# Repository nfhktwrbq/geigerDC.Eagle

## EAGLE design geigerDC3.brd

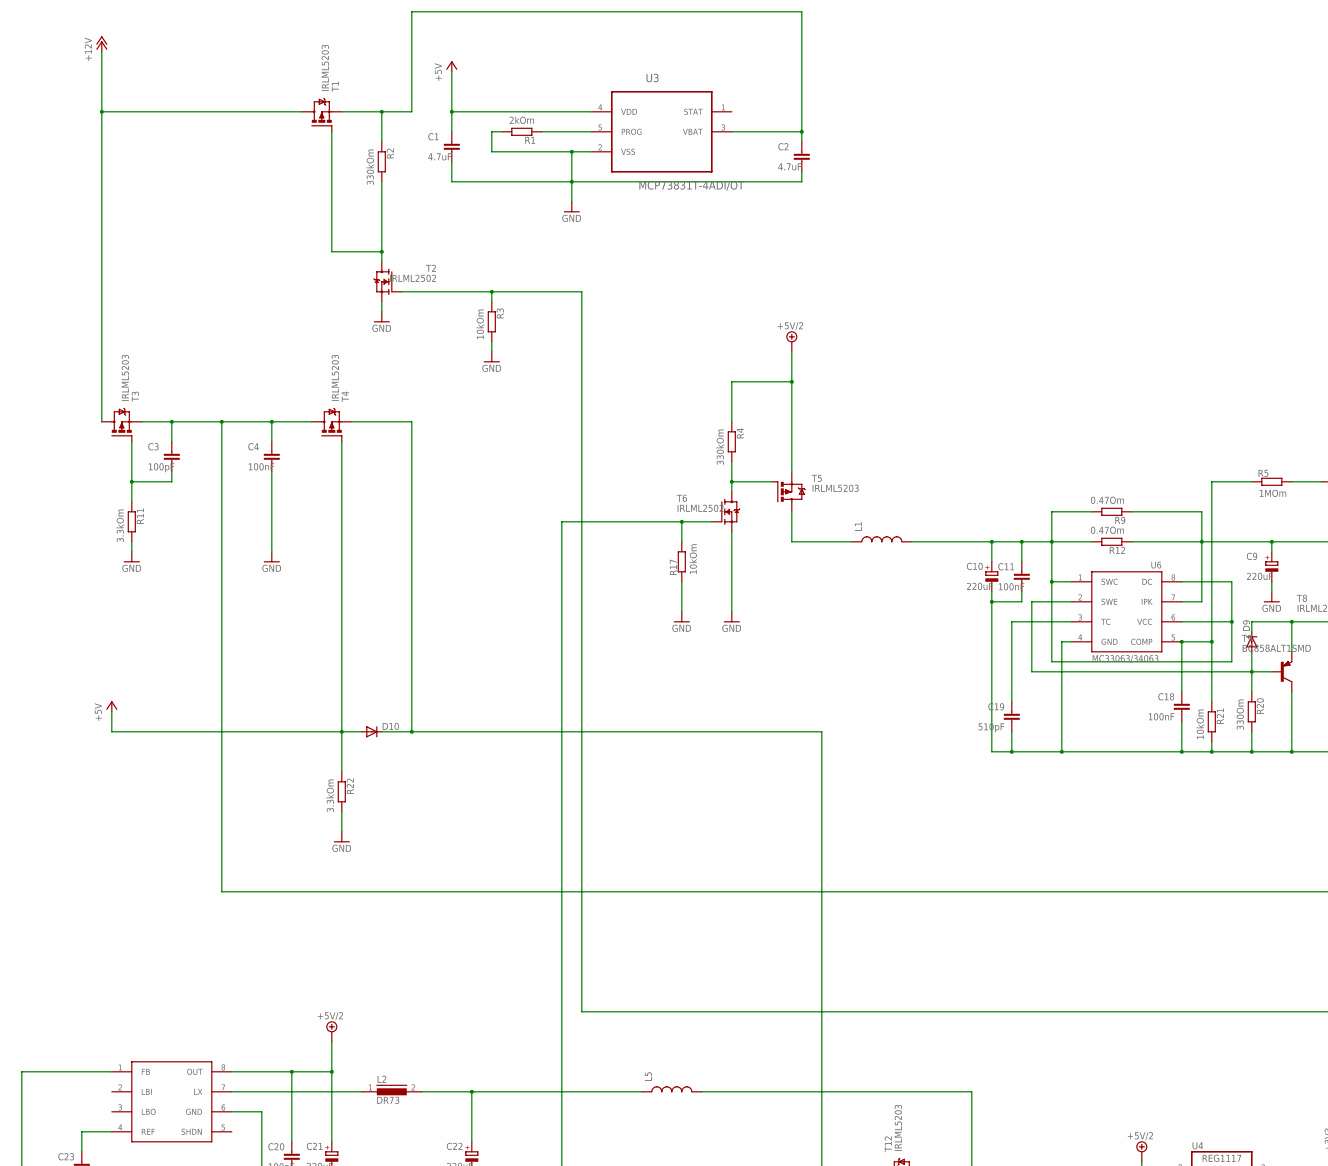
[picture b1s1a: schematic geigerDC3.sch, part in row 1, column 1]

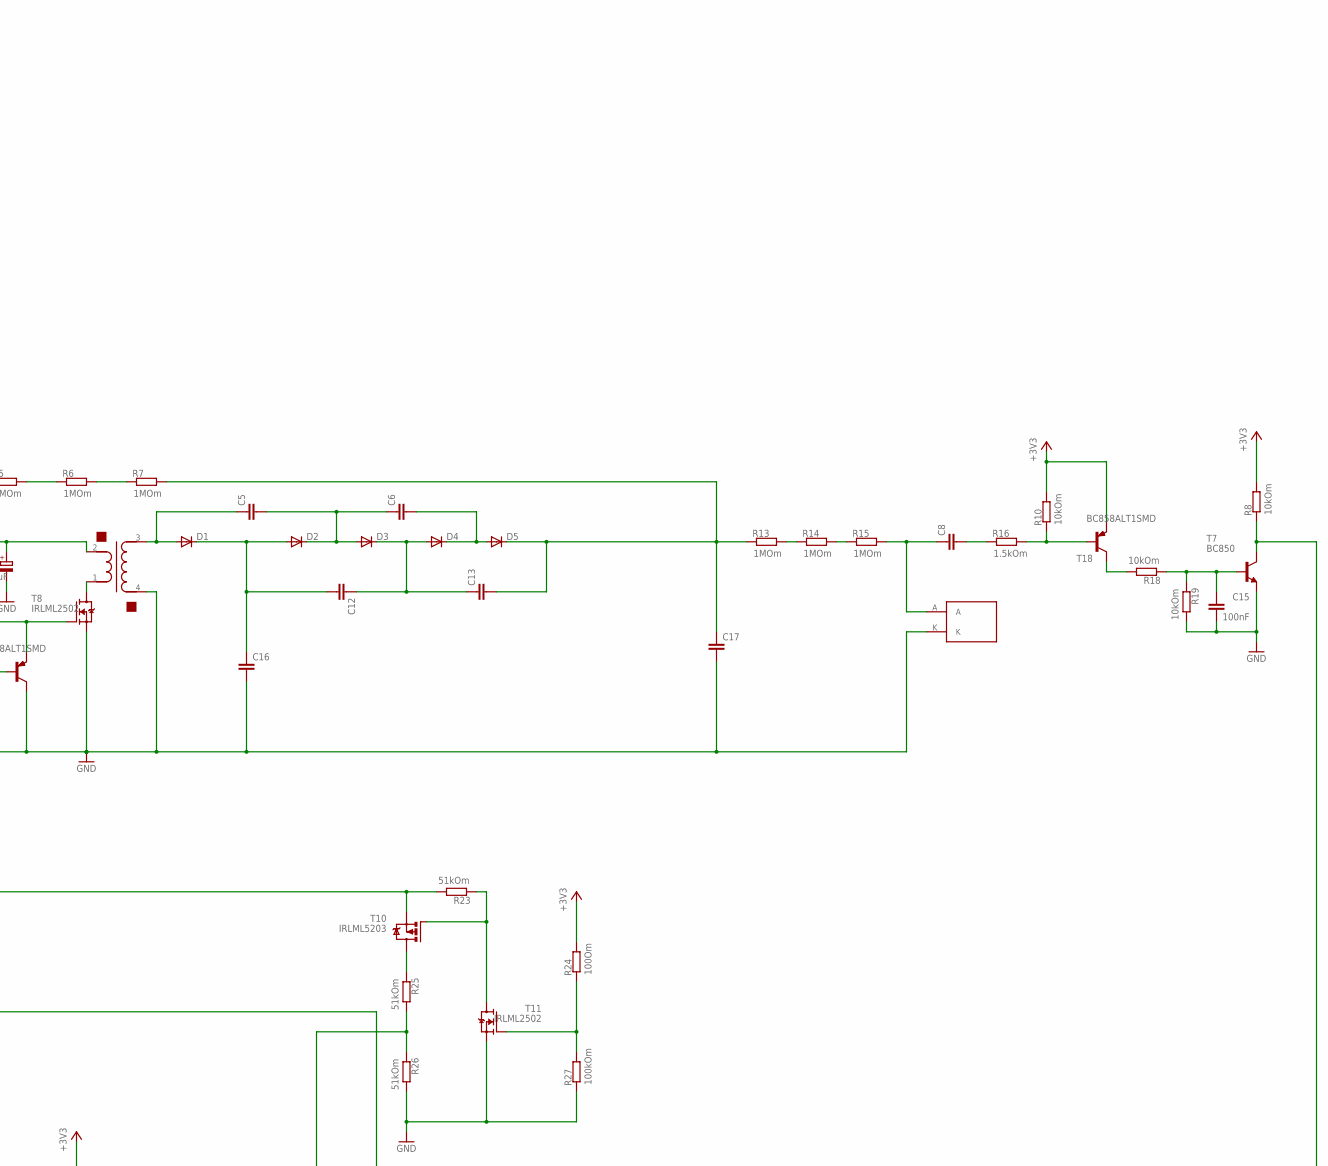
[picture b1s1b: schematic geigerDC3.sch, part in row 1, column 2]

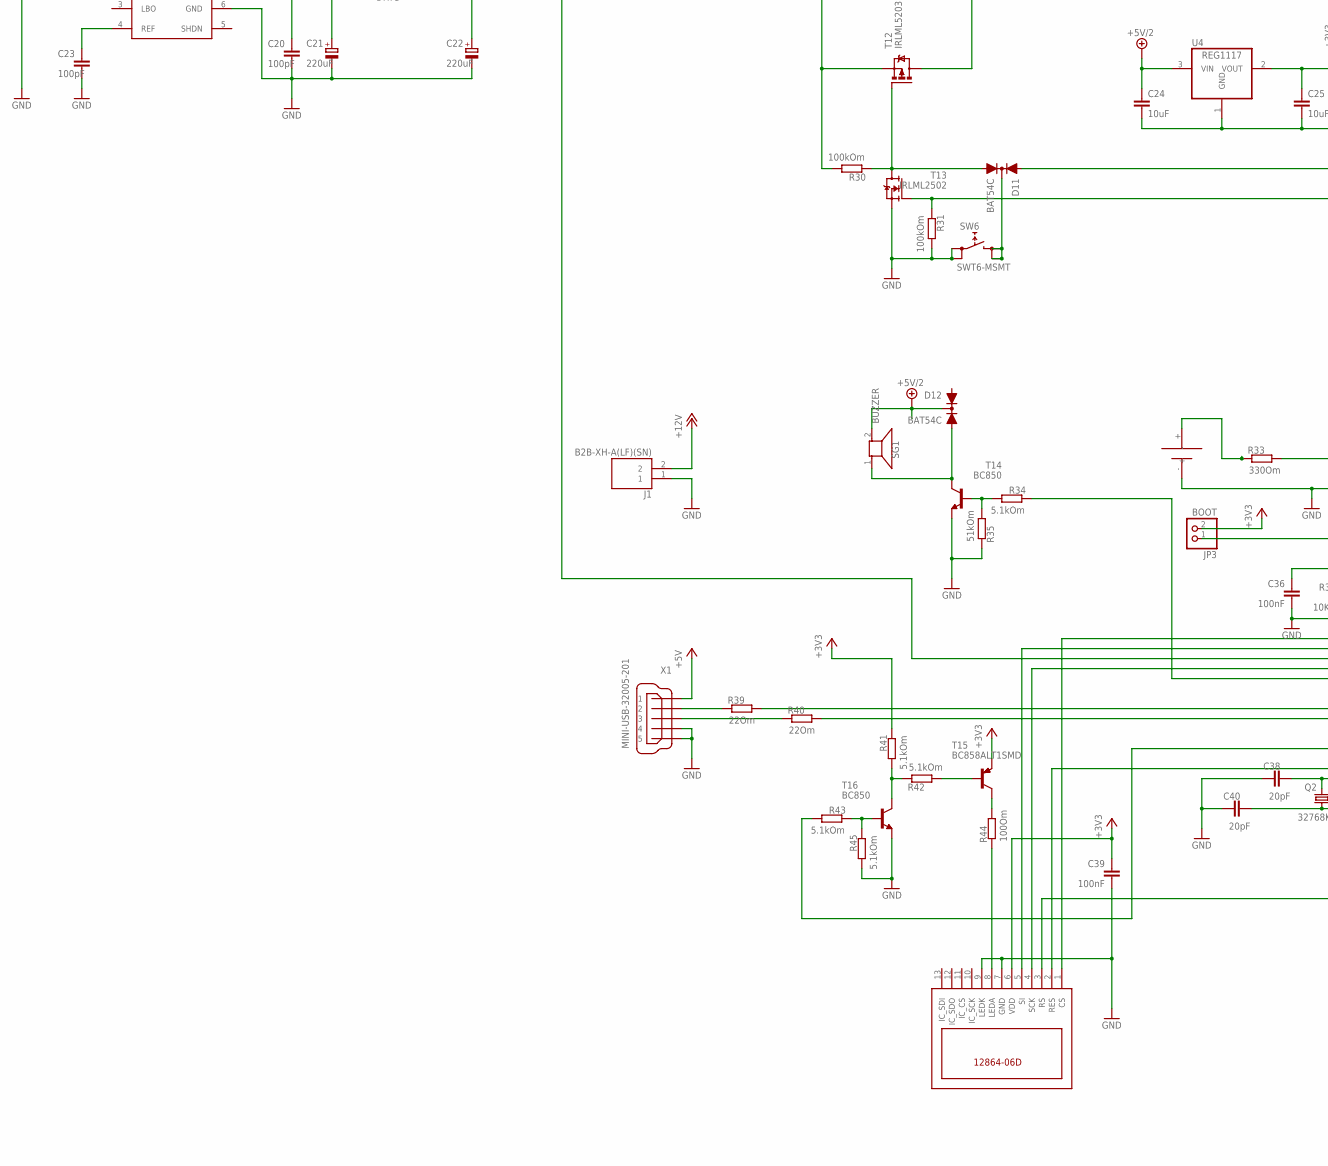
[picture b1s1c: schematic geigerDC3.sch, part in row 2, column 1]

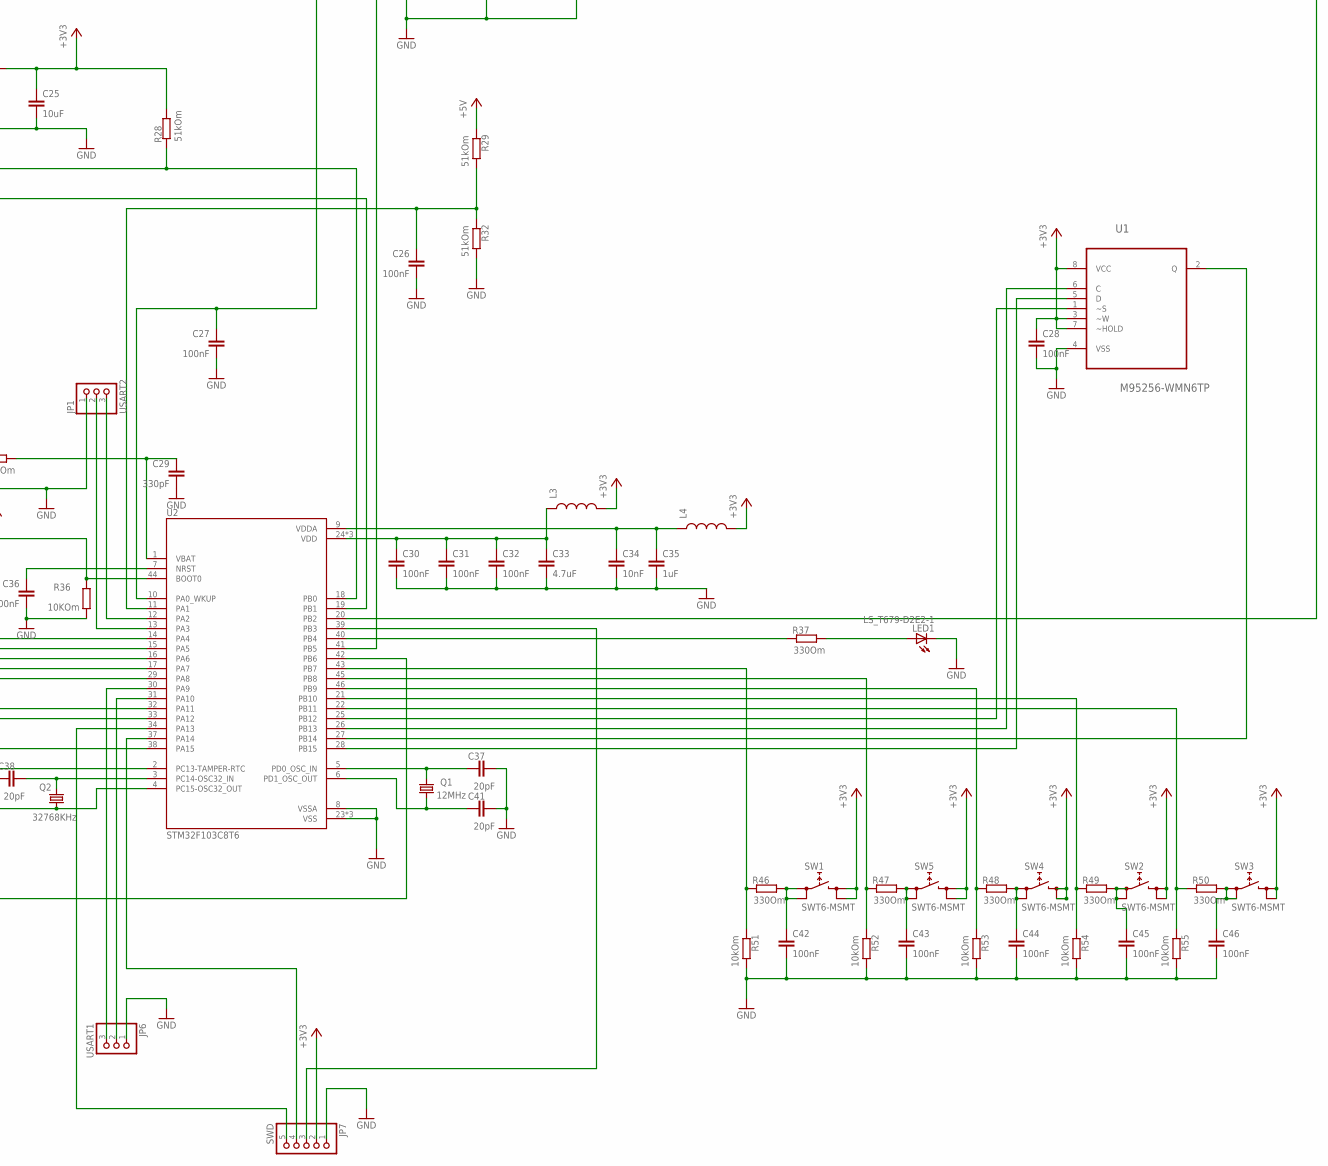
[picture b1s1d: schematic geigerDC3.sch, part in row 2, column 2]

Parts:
C1, C2, C33: 4.7uF; C0402
C3, C20, C23: 100pF; C0402
C4, C11, C15, C18, C26, C27, C28, C30, C31, C32, C36, C39, C42, C43, C44, C45, C46: 100nF; C0402
C5, C6, C12, C13, C16, C17: C-EUC2220K; C2220K
C8: C-EU050-024X044; C050-024X044
C9, C10, C21, C22: 220uF; C/6032-28W
C19: 510pF; C0402
C24, C25: 10uF; C0402
C29: 330pF; C0402
C34: 10nF; C0402
C35: 1uF; C0402
C37, C38, C40, C41: 20pF; C0402
D1, D2, D3, D4, D5: DIODE-DO214BA; DO214BA
D9, D10: DIODE-DO-214AC; DO-214AC
D11, D12: BAT54C; SOT23-R
J1: B2B-XH-A(LF)(SN); JST_B2B-XH-A(LF)(SN)
JP1: USART2; 1X03
JP3: BOOT; 1X02
JP6: USART1; 1X03
JP7: SWD; 1X05
L1, L3, L4, L5: INDUCTOR0805; 0805
L2: DR73
LED1: LS_T679-D2E2-1; PLCC2
Q1: 12MHz; HC49UP
Q2: 32768KHz; 8.2X3.8
R1: 2kOm; R0402
R2, R4: 330kOm; R0402
R3, R8, R10, R17, R18, R19, R51, R52, R53, R54, R55: 10kOm; R0402
R5, R6, R7, R13, R14, R15: 1MOm; R0805
R9, R12: 0.47Om; R0805
R11, R22: 3.3kOm; R0402
R16: 1.5kOm; R0402
R20, R33, R37, R46, R47, R48, R49, R50: 330Om; R0402
R21: 10kOm; R0805
R23, R25, R26, R28, R29, R32, R35: 51kOm; R0402
R24: 100Om; R0402
R27, R30, R31: 100kOm; R0402
R34, R41, R42, R43, R45: 5.1kOm; R0402
R36: 10KOm; R0402
R39, R40: 22Om; R0402
R44: 100Om; R0805
SG1: BUZZER
SW1, SW2, SW3, SW4, SW5, SW6: SWT6-MSMT; SWT6-M
T1, T3, T4, T5, T10, T12: IRLML5203; MICRO3
T2, T6, T8, T11, T13: IRLML2502; SOT23
T7, T14, T16: BC850; SOT23
T9, T15, T18: BC858ALT1SMD; SOT23-BEC
TR1: TRANSFORMER
TUBE: TUBE; XH-B3B
U1: M95256-WMN6TP; SOIC127P600X175-8N
U2: STM32F103C8T6; QFP50P900X900X160-48N
U3: MCP73831T-4ADI/OT; SOT95P280X145-5N
U4: REG1117; SOT223
U5: L6920DTR; TSSOP8
U6: MC33063/MC34063D; SO08
U$1: DS1092-10-W6L
U$5: 12864-06D
X1: MINI-USB-32005-201; 32005-201

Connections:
+3V3: C25.1, C28.1, C39.1, JP3.2, JP7.2, L3.2, L4.2, R8.1, R10.1, R24.1, R28.1, R41.2, SW1.3 (1), SW1.4 (1), SW2.3 (1), SW2.4 (1), SW3.3 (1), SW3.4 (1), SW4.3 (1), SW4.4 (1), SW5.3 (1), SW5.4 (1), T15.E, T18.E, U1.3 (~W), U1.7 (~HOLD), U1.8 (VCC), U4.2 (VOUT), U$5.6 (VDD)
+5V: C1.1, D10.2 (A), R22.2, R29.2, T4.1 (G), U3.4 (VDD), X1.1
+5V/2: C20.1, C21.+, C24.1, D12.3 (C), R4.2, SG1.2, T5.2 (S), U4.3 (VIN), U5.8 (OUT)
+12V: J1.2, T1.3 (D), T3.3 (D)
GND: C1.2, C2.2, C4.2, C9.-, C10.-, C11.2, C15.2, C16.2, C17.2, C18.2, C19.2, C20.2, C21.-, C22.-, C23.2, C24.2, C25.2, C26.2, C27.2, C28.2, C29.2, C30.2, C31.2, C32.2, C33.2, C34.2, C35.2, C36.2, C37.2, C38.1, C39.2, C40.1, C41.2, C42.2, C43.2, C44.2, C45.2, C46.2, J1.1, JP1.1, JP6.1, JP7.1, LED1.C, R1.1, R3.1, R11.1, R17.2, R19.1, R20.1, R21.1, R22.1, R26.1, R27.2, R31.1, R32.1, R35.2, R36.1, R45.1, R51.1, R52.1, R53.1, R54.1, R55.1, SW6.1 (0), SW6.2 (0), T2.2 (S), T6.2 (S), T7.2 (E), T8.2 (S), T9.C, T11.2 (S), T13.2 (S), T14.2 (E), T16.2 (E), TR1.4, TUBE.K, U1.4 (VSS), U2.8 (VSSA), U2.23 (VSS), U2.35 (VSS), U2.47 (VSS), U3.2 (VSS), U4.1 (GND), U5.1 (FB), U5.6 (GND), U6.4 (GND), U$1.-, U$5.7 (GND), U$5.9 (LEDK), X1.4, X1.5
unnamed: C30.1, C31.1, C32.1, C33.1, L3.1, U2.24 (VDD), U2.36 (VDD), U2.48 (VDD)
unnamed: C41.1, Q1.1, U2.6 (PD1_OSC_OUT)
unnamed: C34.1, C35.1, L4.1, U2.9 (VDDA)
unnamed: C37.1, Q1.2, U2.5 (PD0_OSC_IN)
unnamed: C38.2, Q2.4 (2), U2.3 (PC14-OSC32_IN)
unnamed: C36.1, U2.7 (NRST)
unnamed: C40.2, Q2.1, U2.4 (PC15-OSC32_OUT)
unnamed: C29.1, R33.1, U2.1 (VBAT)
unnamed: JP3.1, R36.2, U2.44 (BOOT0)
unnamed: R33.2, U$1.+
unnamed: R40.1, U2.33 (PA12)
unnamed: R39.1, U2.32 (PA11)
unnamed: R39.2, X1.2
unnamed: R40.2, X1.3
unnamed: C2.1, R2.2, T1.2 (S), U3.3 (VBAT)
unnamed: R31.2, T13.1 (G), U2.19 (PB1)
unnamed: D11.2 (A2), R30.2, T12.1 (G), T13.3 (D)
unnamed: D11.3 (C), SW6.3 (1), SW6.4 (1)
unnamed: D11.1 (A1), R28.2, U2.18 (PB0)
unnamed: R3.2, T2.1 (G), U2.41 (PB5)
unnamed: C3.2, R11.2, T3.1 (G)
unnamed: D10.1 (C), R30.1, T4.2 (S), T12.2 (S)
unnamed: L1.1, T5.3 (D)
unnamed: C3.1, C4.1, R23.1, T3.2 (S), T4.3 (D), T10.2 (S)
unnamed: C10.+, C11.1, L1.2, R9.1, R12.1, U6.1 (SWC), U6.6 (VCC), U6.8 (DC)
unnamed: C13.2, C17.1, D5.C, R7.1, R13.2
unnamed: C9.+, R9.2, R12.2, TR1.2, U6.7 (IPK)
unnamed: R4.1, T5.1 (G), T6.3 (D)
unnamed: D9.1 (C), T8.1 (G), T9.E
unnamed: T8.3 (D), TR1.1
unnamed: R17.1, T6.1 (G), U2.16 (PA6)
unnamed: C18.1, R5.2, R21.2, U6.5 (COMP)
unnamed: C5.1, D1.A, TR1.3
unnamed: D9.2 (A), R20.2, T9.B, U6.2 (SWE)
unnamed: R5.1, R6.2
unnamed: R6.1, R7.2
unnamed: R44.2, U$5.8 (LEDA)
unnamed: C43.1, R47.1, SW5.1 (0), SW5.2 (0)
unnamed: R24.2, R27.1, T11.1 (G)
unnamed: C19.1, U6.3 (TC)
unnamed: JP6.2, U2.31 (PA10)
unnamed: C27.1, R25.1, R26.2, U2.10 (PA0_WKUP)
unnamed: R23.2, T10.1 (G), T11.3 (D)
unnamed: R2.1, T1.1 (G), T2.3 (D)
unnamed: C12.2, C16.1, D1.C, D2.A
unnamed: C5.2, C6.1, D2.C, D3.A
unnamed: C12.1, C13.1, D3.C, D4.A
unnamed: C6.2, D4.C, D5.A
unnamed: C44.1, R48.1, SW4.1 (0), SW4.2 (0)
unnamed: JP1.3, U2.12 (PA2)
unnamed: JP1.2, U2.13 (PA3)
unnamed: R25.2, T10.3 (D)
unnamed: JP6.3, U2.30 (PA9)
unnamed: R13.1, R14.2
unnamed: R14.1, R15.2
unnamed: C8.1, R15.1, TUBE.A
unnamed: C8.2, R16.2
unnamed: R10.2, R16.1, T18.B
unnamed: JP7.5, U2.34 (PA13)
unnamed: R18.1, T18.C
unnamed: C15.1, R18.2, R19.2, T7.1 (B)
unnamed: R8.2, T7.3 (C), U2.20 (PB2)
unnamed: JP7.4, U2.37 (PA14)
unnamed: JP7.3, U2.39 (PB3)
unnamed: U1.5 (D), U2.28 (PB15)
unnamed: U1.2 (Q), U2.27 (PB14)
unnamed: U1.6 (C), U2.26 (PB13)
unnamed: R49.2, R54.2, U2.21 (PB10)
unnamed: C46.1, R50.1, SW3.1 (0), SW3.2 (0)
unnamed: U1.1 (~S), U2.25 (PB12)
unnamed: C45.1, R49.1, SW2.1 (0), SW2.2 (0)
unnamed: C42.1, R46.1, SW1.1 (0), SW1.2 (0)
unnamed: C26.1, R29.1, R32.2, U2.11 (PA1)
unnamed: R46.2, R51.2, U2.43 (PB7)
unnamed: R47.2, R52.2, U2.45 (PB8)
unnamed: R48.2, R53.2, U2.46 (PB9)
unnamed: R50.2, R55.2, U2.22 (PB11)
unnamed: R34.2, U2.29 (PA8)
unnamed: D12.2 (A2), SG1.1, T14.3 (C)
unnamed: U2.14 (PA4), U$5.1 (CS)
unnamed: R34.1, R35.1, T14.1 (B)
unnamed: U2.15 (PA5), U$5.5 (SI)
unnamed: U2.17 (PA7), U$5.4 (SCK)
unnamed: R44.1, T15.C
unnamed: C22.+, L2.2, L5.1
unnamed: R42.1, T15.B
unnamed: R41.1, R42.2, T16.3 (C)
unnamed: R37.2, U2.40 (PB4)
unnamed: R43.2, R45.2, T16.1 (B)
unnamed: LED1.A, R37.1
unnamed: R43.1, U2.38 (PA15)
unnamed: U2.2 (PC13-TAMPER-RTC), U$5.2 (RES)
unnamed: U2.42 (PB6), U$5.3 (RS)
unnamed: R1.2, U3.5 (PROG)
unnamed: C23.1, U5.4 (REF)
unnamed: L2.1, U5.7 (LX)
unnamed: L5.2, T12.3 (D)

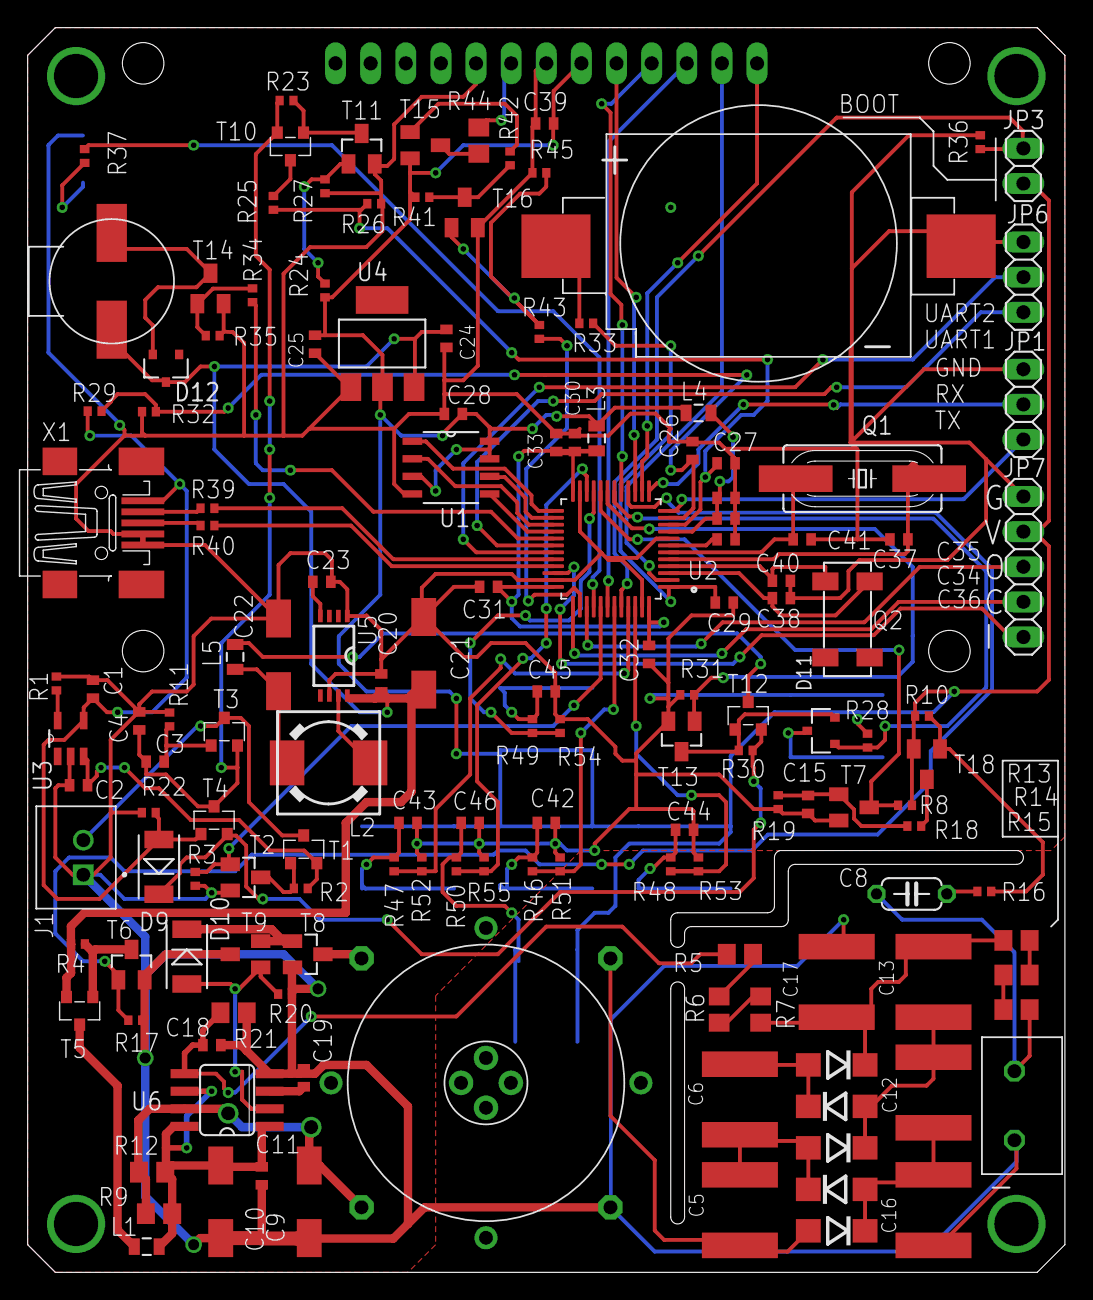
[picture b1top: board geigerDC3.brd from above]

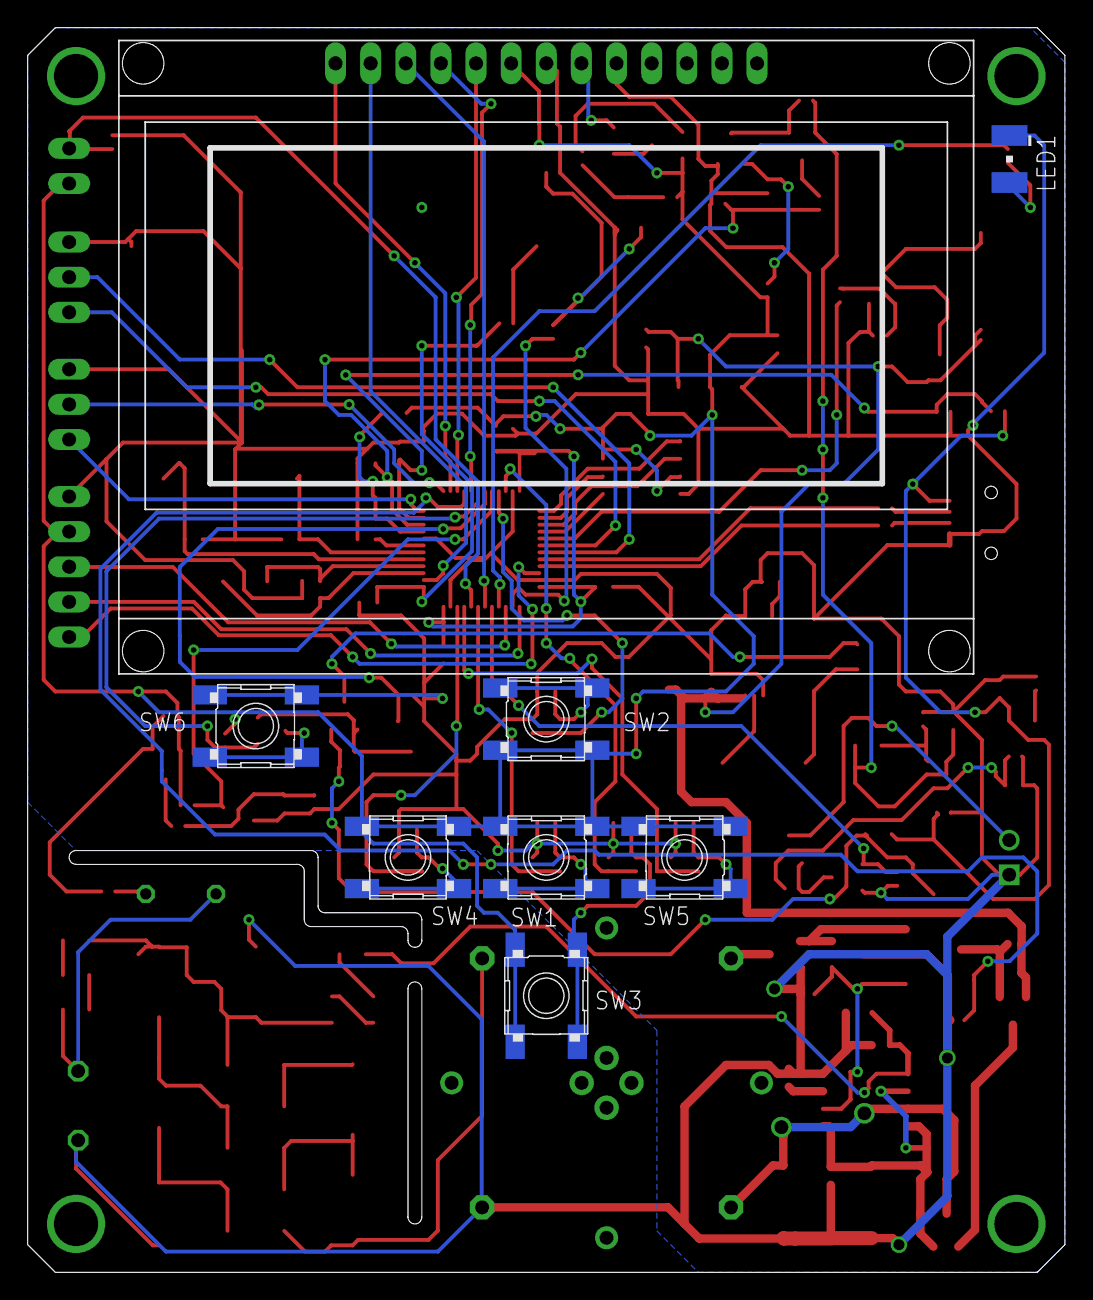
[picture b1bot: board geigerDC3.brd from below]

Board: 2 copper layers, 75.0 x 90.0 mm, 155 parts (8 on the bottom side), 102 nets.

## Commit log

2020-03-13 start routing
2020-03-14 change MCU orientation
2020-03-16 Almost all routing
2020-03-17 Edit board and generete gerber
2020-06-29 add notes

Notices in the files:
parts and their libraries:
SparkFun: Licensing: CC v3.0 Share-Alike You are welcome to use this library for commercial purposes.
crystal-geyer_V1_0: Copyright: Geyer-Electronic
